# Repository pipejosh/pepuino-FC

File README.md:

This the next gen FC designed for a rocket (it's still in progress)

## Schematic

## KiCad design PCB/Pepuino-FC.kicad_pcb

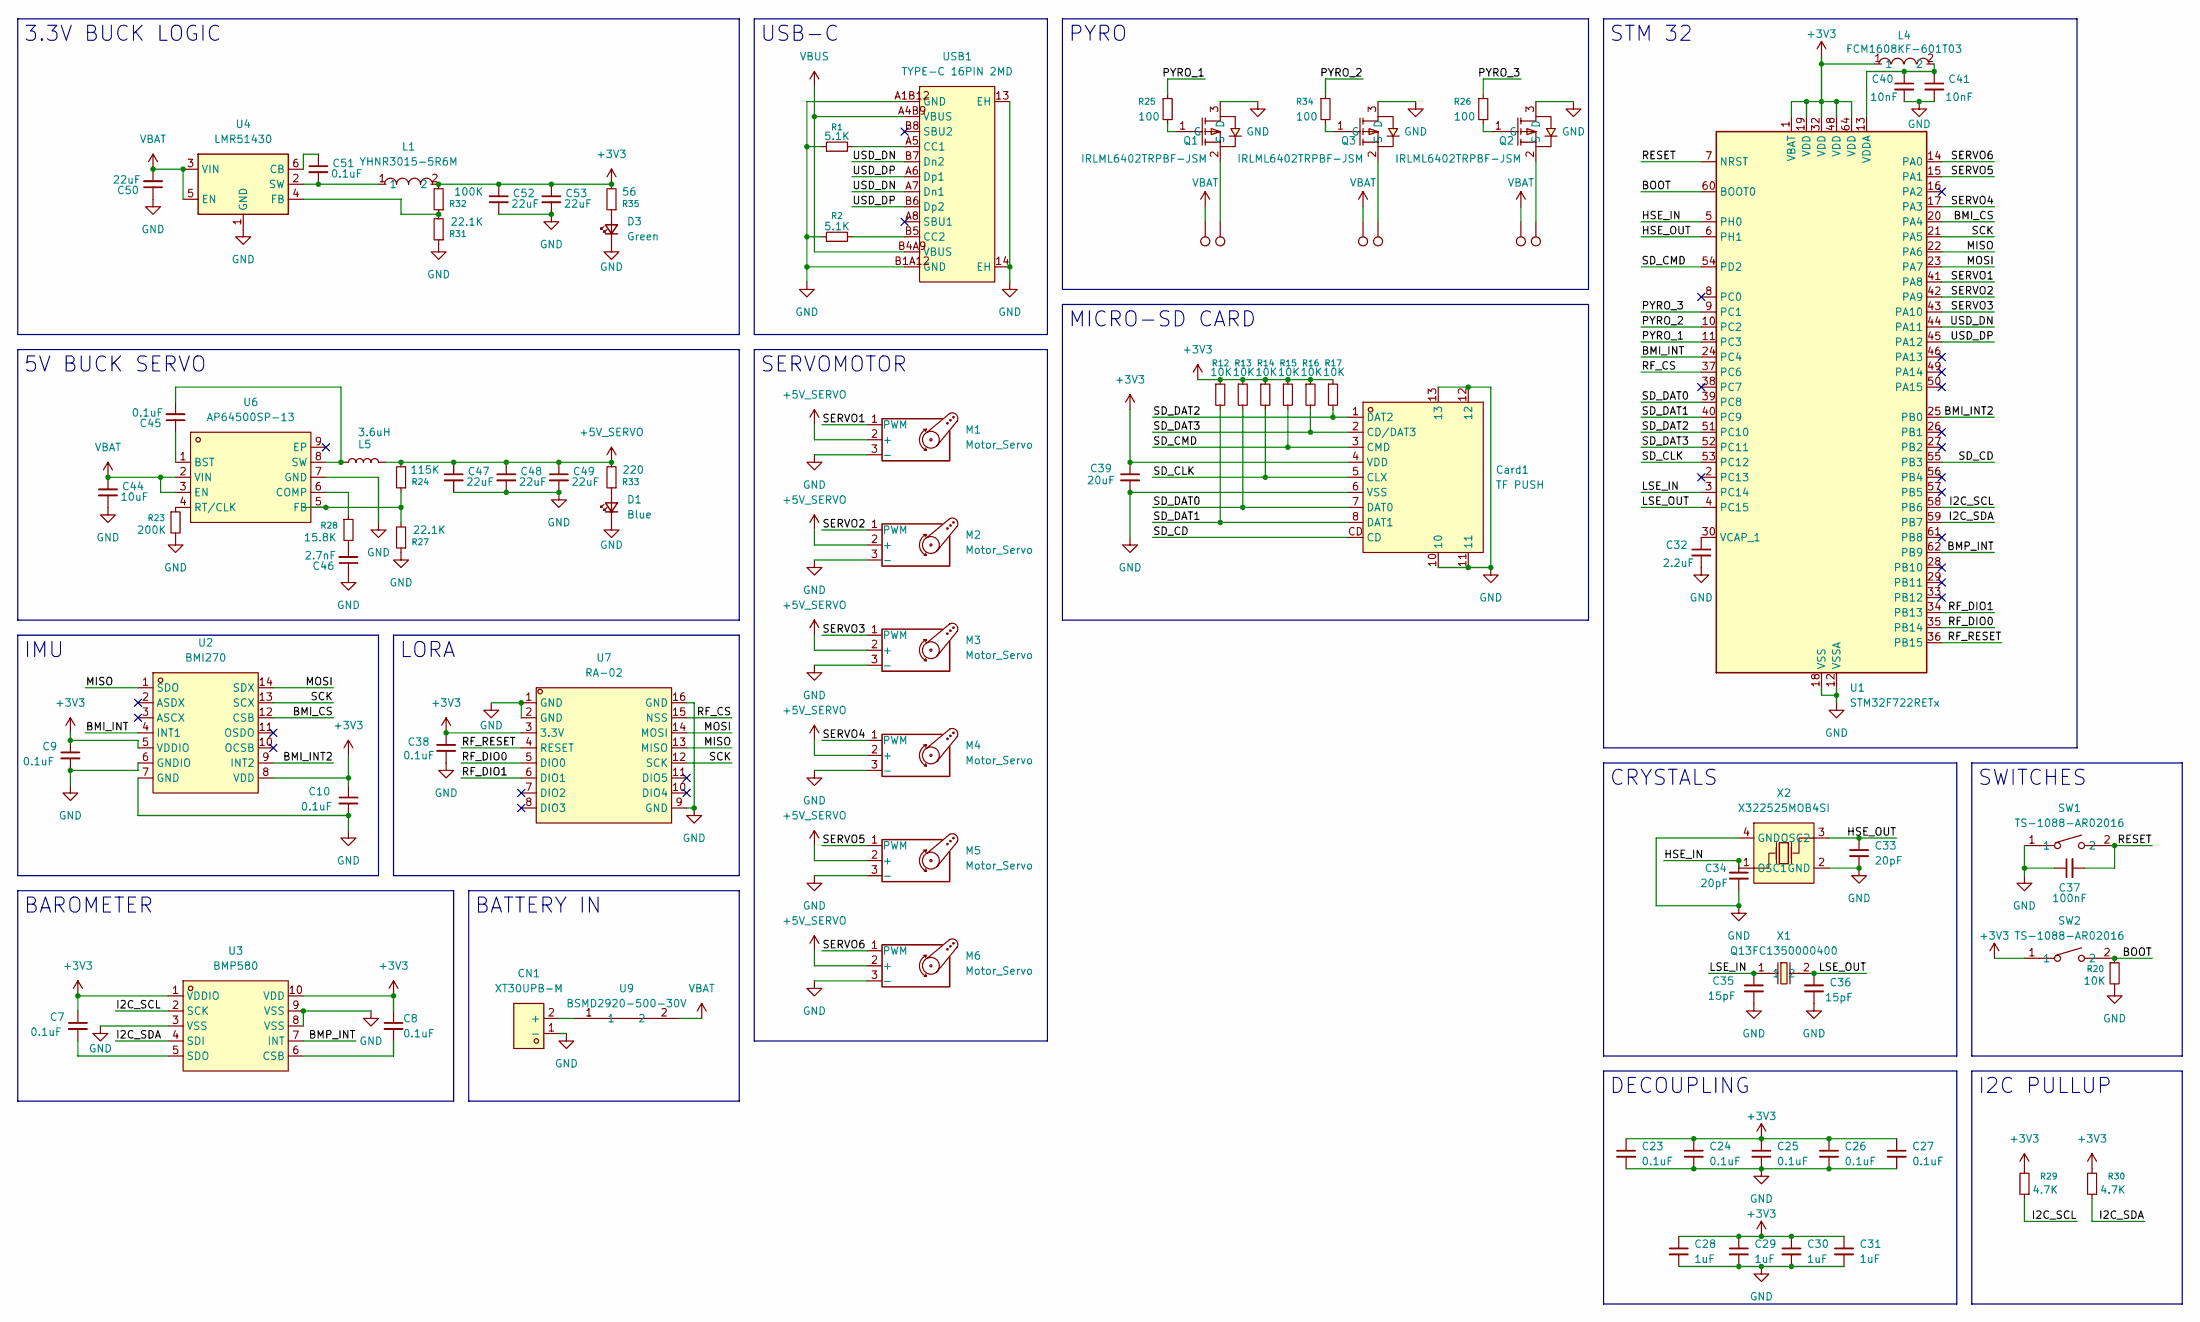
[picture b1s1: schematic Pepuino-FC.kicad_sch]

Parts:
C7, C8, C9, C10, C23, C24, C25, C26, C27, C38: 0.1uF; C_0402_1005Metric
C28, C29, C30, C31: 1uF; C_0402_1005Metric
C32: 2.2uF; C_0402_1005Metric
C33, C34: 20pF; C_0402_1005Metric
C35, C36: 15pF; C_0402_1005Metric
C37: 100nF; C_0402_1005Metric
C39: 20uF; C_0402_1005Metric
C40, C41: 10nF; C_0402_1005Metric
C44: 10uF; C_0805_2012Metric
C45, C51: 0.1uF; C_0805_2012Metric
C46: 2.7nF; C_0805_2012Metric
C47, C48, C49, C50, C52, C53: 22uF; C_0805_2012Metric
CN1: XT30UPB-M; CONN-TH_XT30UPB-M; MPN XT30UPB-M; LCSC Part C428721
Card1: TF PUSH; TF-SMD_TF-PUSH; MPN TF PUSH; LCSC Part C393941
D1: Blue; LED_0805_2012Metric
D3: Green; LED_0805_2012Metric
L1: YHNR3015-5R6M; IND-SMD_L3.0-W3.0; MPN YHNR3015-5R6M; LCSC Part C18236327
L4: FCM1608KF-601T03; L0603; MPN FCM1608KF-601T03; LCSC Part C141723
L5: 3.6uH; L_0402_1005Metric
M1, M2, M3, M4, M5, M6: Motor_Servo; PinHeader_1x03_P1.00mm_Vertical
Q1, Q2, Q3: IRLML6402TRPBF-JSM; SOT-23-3_L2.9-W1.3-P1.90-LS2.4-BR; MPN IRLML6402TRPBF-JSM; LCSC Part C18190991
R1, R2: 5.1K; R_0201_0603Metric
R12, R13, R14, R15, R16, R17, R20: 10K; R_0201_0603Metric
R23: 200K; R_0201_0603Metric
R24: 115K; R_0201_0603Metric
R25, R26, R34: 100; R_0201_0603Metric
R27, R31: 22.1K; R_0201_0603Metric
R28: 15.8K; R_0201_0603Metric
R29, R30: 4.7K; R_0201_0603Metric
R32: 100K; R_0201_0603Metric
R33: 220; R_0201_0603Metric
R35: 56; R_0201_0603Metric
SW1, SW2: TS-1088-AR02016; SW-SMD_L3.9-W3.0-P4.45; MPN TS-1088-AR02016; LCSC Part C720477
TP1, TP2, TP3, TP4, TP5, TP6: TestPoint; TestPoint_Pad_D2.0mm
U1: STM32F722RETx; LQFP-64_10x10mm_P0.5mm
U2: BMI270; LGA-14_L3.0-W2.5-P0.50-BR; MPN BMI270; LCSC Part C2836813
U3: BMP580; LGA-10_L2.0-W2.0-P0.50-TL_BMP580; MPN BMP580; LCSC Part C22391138
U4: LMR51430; SOT-23-6
U6: AP64500SP-13; SO-8_L4.9-W3.9-P1.27-LS6.0-BL-EP; MPN AP64500SP-13; LCSC Part C2070920
U7: RA-02; WIRELM-SMD_RA-02-BL; MPN Ra-02; LCSC Part C90039
U9: BSMD2920-500-30V; F2920; MPN BSMD2920-500-30V; LCSC Part C20539728
USB1: TYPE-C 16PIN 2MD; USB-C-SMD_TYPE-C-16PIN-2MD-073; MPN TYPE-C 16PIN 2MD(073); LCSC Part C2765186
X1: Q13FC1350000400; FC-135R_L3.2-W1.5; MPN Q13FC13500004; LCSC Part C32346
X2: X322525MOB4SI; CRYSTAL-SMD_4P-L3.2-W2.5-BL; MPN X322525MOB4SI; LCSC Part C9006

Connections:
+3V3: C7.1, C8.1, C9.1, C10.1, C23.1, C24.1, C25.1, C26.1, C27.1, C28.1, C29.1, C30.1, C31.1, C38.1, C39.1, C52.1, C53.1, Card1.4 (VDD), L1.2, L4.1, R12.1, R13.1, R14.1, R15.1, R16.1, R17.1, R29.2, R30.2, R32.2, R35.2, SW2.1, U1.1 (VBAT), U1.19 (VDD), U1.32 (VDD), U1.48 (VDD), U1.64 (VDD), U2.5 (VDDIO), U2.8 (VDD), U3.1 (VDDIO), U3.10 (VDD), U7.3 (3.3V)
+5V_SERVO: C47.1, C48.1, C49.1, L5.2, M1.2 (+), M2.2 (+), M3.2 (+), M4.2 (+), M5.2 (+), M6.2 (+), R24.2, R33.2
/BMI_CS: U1.20 (PA4), U2.12 (CSB)
/BMI_INT: U1.24 (PC4), U2.4 (INT1)
/BMI_INT2: U1.25 (PB0), U2.9 (INT2)
/BMP_INT: U1.62 (PB9), U3.7 (INT)
/BOOT: R20.1, SW2.2, U1.60 (BOOT0)
/HSE_IN: C34.1, U1.5 (PH0), X2.1 (OSC1)
/HSE_OUT: C33.1, U1.6 (PH1), X2.3 (OSC2)
/I2C_SCL: R29.1, U1.58 (PB6), U3.2 (SCK)
/I2C_SDA: R30.1, U1.59 (PB7), U3.4 (SDI)
/LSE_IN: C35.1, U1.3 (PC14), X1.1
/LSE_OUT: C36.1, U1.4 (PC15), X1.2
/MISO: U1.22 (PA6), U2.1 (SDO), U7.13 (MISO)
/MOSI: U1.23 (PA7), U2.14 (SDX), U7.14 (MOSI)
/PYRO_1: R25.1, U1.11 (PC3)
/PYRO_2: R34.1, U1.10 (PC2)
/PYRO_3: R26.1, U1.9 (PC1)
/RESET: C37.2, SW1.2, U1.7 (NRST)
/RF_CS: U1.37 (PC6), U7.15 (NSS)
/RF_DIO0: U1.35 (PB14), U7.5 (DIO0)
/RF_DIO1: U1.34 (PB13), U7.6 (DIO1)
/RF_RESET: U1.36 (PB15), U7.4 (RESET)
/SCK: U1.21 (PA5), U2.13 (SCX), U7.12 (SCK)
/SD_CD: Card1.CD, U1.55 (PB3)
/SD_CLK: Card1.5 (CLX), R14.2, U1.53 (PC12)
/SD_CMD: Card1.3 (CMD), R15.2, U1.54 (PD2)
/SD_DAT0: Card1.7 (DAT0), R13.2, U1.39 (PC8)
/SD_DAT1: Card1.8 (DAT1), R12.2, U1.40 (PC9)
/SD_DAT2: Card1.1 (DAT2), R17.2, U1.51 (PC10)
/SD_DAT3: Card1.2 (CD/DAT3), R16.2, U1.52 (PC11)
/SERVO1: M1.1 (PWM), U1.41 (PA8)
/SERVO2: M2.1 (PWM), U1.42 (PA9)
/SERVO3: M3.1 (PWM), U1.43 (PA10)
/SERVO4: M4.1 (PWM), U1.17 (PA3)
/SERVO5: M5.1 (PWM), U1.15 (PA1)
/SERVO6: M6.1 (PWM), U1.14 (PA0)
/USD_DN: U1.44 (PA11), USB1.A7 (Dn1), USB1.B7 (Dn2)
/USD_DP: U1.45 (PA12), USB1.A6 (Dp1), USB1.B6 (Dp2)
GND: C9.2, C10.2, C23.2, C24.2, C25.2, C26.2, C27.2, C28.2, C29.2, C30.2, C31.2, C32.2, C33.2, C34.2, C35.2, C36.2, C37.1, C38.2, C39.2, C40.2, C41.2, C44.2, C46.1, C47.2, C48.2, C49.2, C50.1, C52.2, C53.2, CN1.1 (-), Card1.6 (VSS), Card1.10, Card1.11, Card1.12, Card1.13, D1.1 (K), D3.1 (K), M1.3 (-), M2.3 (-), M3.3 (-), M4.3 (-), M5.3 (-), M6.3 (-), Q1.3 (D), Q2.3 (D), Q3.3 (D), R1.1, R2.1, R20.2, R23.2, R27.1, R31.1, SW1.1, U1.12 (VSSA), U1.18 (VSS), U1.31 (VSS), U1.47 (VSS), U1.63 (VSS), U2.6 (GNDIO), U2.7 (GND), U3.3 (VSS), U3.8 (VSS), U3.9 (VSS), U4.1 (GND), U6.7 (GND), U7.1 (GND), U7.2 (GND), U7.9 (GND), U7.16 (GND), USB1.13 (EH), USB1.14 (EH), USB1.A1B12 (GND), USB1.B1A12 (GND), X2.2 (GND), X2.4 (GND)
unnamed: C46.2, R28.2
unnamed: CN1.2 (+), U9.1
unnamed: D1.2 (A), R33.1
unnamed: D3.2 (A), R35.1
unnamed: Q1.1 (G), R25.2
unnamed: Q1.2 (S), TP4.1 (1_1)
unnamed: Q2.1 (G), R26.2
unnamed: Q2.2 (S), TP1.1 (1_1)
unnamed: Q3.1 (G), R34.2
unnamed: Q3.2 (S), TP6.1 (1_1)
unnamed: C32.1, U1.30 (VCAP_1)
unnamed: C40.1, C41.1, L4.2, U1.13 (VDDA)
unnamed: C8.2, U3.6 (CSB)
unnamed: C7.2, U3.5 (SDO)
unnamed: C51.1, U4.6 (CB)
unnamed: R31.2, R32.1, U4.4 (FB)
unnamed: C51.2, L1.1, U4.2 (SW)
unnamed: C45.1, U6.1 (BST)
unnamed: R28.1, U6.6 (COMP)
unnamed: R24.1, R27.2, U6.5 (FB)
unnamed: R23.1, U6.4 (RT/CLK)
unnamed: C45.2, L5.1, U6.8 (SW)
unnamed: R1.2, USB1.A5 (CC1)
unnamed: R2.2, USB1.B5 (CC2)
VBAT: C44.1, C50.2, TP2.1 (1_1), TP3.1 (1_1), TP5.1 (1_1), U4.3 (VIN), U4.5 (EN), U6.2 (VIN), U6.3 (EN), U9.2
VBUS: USB1.A4B9 (VBUS), USB1.B4A9 (VBUS)

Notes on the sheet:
SERVOMOTOR
I2C PULLUP
USB-C
5V BUCK SERVO
BATTERY IN
LORA
BAROMETER
DECOUPLING
CRYSTALS
SWITCHES
PYRO
STM 32
3.3V BUCK LOGIC
MICRO-SD CARD
IMU

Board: 4 copper layers, 93 parts (0 on the bottom side), 66 nets, no tracks yet.

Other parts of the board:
H1, H2, H3, H4: MountingScrew; MountingHole_2.2mm_M2_DIN965_Pad

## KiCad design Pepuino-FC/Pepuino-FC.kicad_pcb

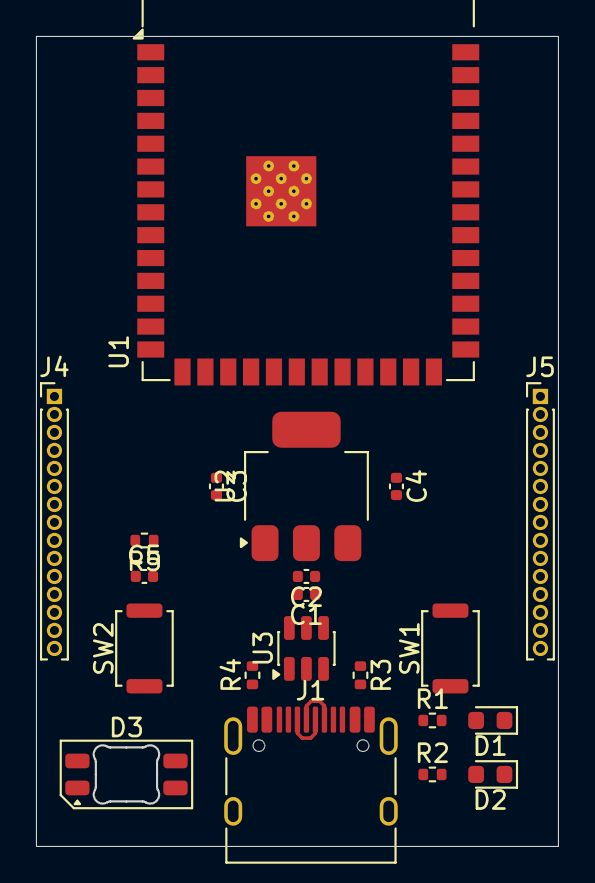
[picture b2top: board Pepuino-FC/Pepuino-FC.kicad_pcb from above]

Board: 2 copper layers, 28.9 x 44.9 mm, 21 parts (0 on the bottom side), 34 nets.

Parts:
C1, C4: 100n; C_0402_1005Metric
C2, C5: 10u; C_0402_1005Metric
C3: 22u; C_0402_1005Metric
D1, D2: LED; LED_0603_1608Metric
D3: SK6812MINI-E; LED_SK6812MINI-E_3.2x2.8mm_P1.5mm_ReverseMount
J1: USB_C_Receptacle_USB2.0_16P; USB_C_Receptacle_HRO_TYPE-C-31-M-12
J4, J5: Conn_01x15_Pin; PinHeader_1x15_P1.00mm_Vertical
R1, R2, R3, R4, R5: 5.1K; R_0402_1005Metric
SW1, SW2: Switch; SW_Push_SPST_NO_Alps_SKRK
U1: ESP32-S3-WROOM-1
U2: LD1117S33TR_SOT223; SOT-223-3_TabPin2
U3: USBLC6-2SC6; SOT-23-6

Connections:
+3V3: C2.1, C3.1, C4.1, J4.2, J5.2, R2.1, R5.1, U2.2 (VO)
D+: U1.14 (USB_D+), U3.4 (I/O2)
D-: U1.13 (USB_D-), U3.6 (I/O1)
EN: C5.1, J4.4, R5.2, SW2.2, U1.3 (EN)
GND: C1.2, C2.2, C3.2, C4.2, C5.2, D1.1 (K), D2.1 (K), D3.1 (VSS), J1.A1 (GND), J1.A12 (GND), J1.B1 (GND), J1.B12 (GND), J1.SH (SHIELD), J4.1, J4.15, J5.1, J5.15, R3.1, R4.2, SW1.1, SW2.1, U1.1 (GND), U1.40 (GND), U1.41 (GND), U2.1 (GND), U3.2 (GND)
GPIO0: SW1.2, U1.27 (IO0)
GPIO2: J5.4, U1.38 (IO2)
GPIO3: J4.14, U1.15 (IO3)
GPIO4: J4.5, U1.4 (IO4)
GPIO5: J4.6, U1.5 (IO5)
GPIO6: J4.7, U1.6 (IO6)
GPIO7: J4.8, U1.7 (IO7)
GPIO8: J4.13, U1.12 (IO8)
GPIO9: J5.14, U1.17 (IO9)
GPIO10: J5.13, U1.18 (IO10)
GPIO11: J5.12, U1.19 (IO11)
GPIO12: J5.11, U1.20 (IO12)
GPIO13: J5.10, U1.21 (IO13)
GPIO14: J5.9, U1.22 (IO14)
GPIO15: J4.9, U1.8 (IO15)
GPIO16: J4.10, U1.9 (IO16)
GPIO17: J4.11, U1.10 (IO17)
GPIO18: J4.12, U1.11 (IO18)
GPIO21: D3.2 (DIN), J5.8, U1.23 (IO21)
GPIO38: J5.5, U1.31 (IO38)
GPIO47: J5.7, U1.24 (IO47)
GPIO48: J5.6, U1.25 (IO48)
unnamed: D1.2 (A), R1.2
unnamed: D2.2 (A), R2.2
unnamed: J1.A5 (CC1), R4.1
unnamed: J1.B5 (CC2), R3.2
unnamed: J1.A6 (D+), J1.B6 (D+), U3.3 (I/O2)
unnamed: J1.A7 (D-), J1.B7 (D-), U3.1 (I/O1)
VBUS: C1.1, D3.3 (VDD), J1.A4 (VBUS), J1.A9 (VBUS), J1.B4 (VBUS), J1.B9 (VBUS), J4.3, J5.3, R1.1, U2.3 (VI), U3.5 (VBUS)

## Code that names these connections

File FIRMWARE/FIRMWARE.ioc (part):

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Mcu.Name=STM32F722R(C-E)Tx
Mcu.Package=LQFP64
Mcu.UserName=STM32F722RETx
PA0-WKUP.Signal=S_TIM2_CH1_ETR
PA1.Signal=S_TIM2_CH2
PA10.Signal=S_TIM1_CH3
PA11.Mode=Host_Only
PA11.Signal=USB_OTG_FS_DM
PA12.Mode=Host_Only
PA12.Signal=USB_OTG_FS_DP
PA2.Signal=S_TIM2_CH3
PA3.Signal=S_TIM2_CH4
PA4.GPIOParameters=GPIO_Label
PA4.GPIO_Label=ICM_CS
PA4.Mode=NSS_Signal_Hard_Output
PA4.Signal=SPI1_NSS
PA5.Mode=Full_Duplex_Master
PA5.Signal=SPI1_SCK
PA6.Mode=Full_Duplex_Master
PA6.Signal=SPI1_MISO
PA7.Mode=Full_Duplex_Master
PA7.Signal=SPI1_MOSI
PA8.Signal=S_TIM1_CH1
PA9.Signal=S_TIM1_CH2
PB0.GPIOParameters=GPIO_Label
PB0.GPIO_Label=ICM_INT2
PB0.Signal=GPXTI0
PB1.Signal=GPIO_Output
PB13.GPIOParameters=GPIO_Label
PB13.GPIO_Label=RF_DIO1
PB13.Signal=GPIO_Input
PB14.GPIOParameters=GPIO_Label
PB14.GPIO_Label=RF_DIO0
PB14.Signal=GPIO_Input
PB15.GPIOParameters=GPIO_Label
PB15.GPIO_Label=RF_RST
PB15.Signal=GPIO_Output
PB3.GPIOParameters=GPIO_Label
PB3.GPIO_Label=SD_CS
PB3.Signal=GPIO_Output
PB5.GPIOParameters=GPIO_Label
PB5.GPIO_Label=BQ_INT
PB5.Signal=GPXTI5
PB6.Mode=I2C
PB6.Signal=I2C1_SCL
PB7.Mode=I2C
PB7.Signal=I2C1_SDA
PB8.GPIOParameters=GPIO_Label
PB8.GPIO_Label=BQ_CE
PB8.Signal=GPIO_Output
PB9.GPIOParameters=GPIO_Label
PB9.GPIO_Label=BMP_INT
PB9.Signal=GPIO_Output
PC1.GPIOParameters=GPIO_Label
PC1.GPIO_Label=PYRO_2
PC1.Signal=GPIO_Output
PC10.Mode=SD_4_bits_Wide_bus
PC10.Signal=SDMMC1_D2
PC11.Mode=SD_4_bits_Wide_bus
PC11.Signal=SDMMC1_D3
PC12.Mode=SD_4_bits_Wide_bus
PC12.Signal=SDMMC1_CK
PC14-OSC32_IN.Mode=LSE-External-Oscillator
PC14-OSC32_IN.Signal=RCC_OSC32_IN
PC15-OSC32_OUT.Mode=LSE-External-Oscillator
PC15-OSC32_OUT.Signal=RCC_OSC32_OUT
PC2.GPIOParameters=GPIO_Label
PC2.GPIO_Label=PYRO_1
PC2.Signal=GPIO_Output
PC4.GPIOParameters=GPIO_Label
PC4.GPIO_Label=ICM_INT1
PC4.Signal=GPXTI4
PC6.GPIOParameters=GPIO_Label
PC6.GPIO_Label=RF_CS
PC6.Signal=GPIO_Output
PC8.Mode=SD_4_bits_Wide_bus
PC8.Signal=SDMMC1_D0
PC9.Mode=SD_4_bits_Wide_bus
PC9.Signal=SDMMC1_D1
PD2.Mode=SD_4_bits_Wide_bus
PD2.Signal=SDMMC1_CMD
PH0-OSC_IN.Mode=HSE-External-Oscillator
PH0-OSC_IN.Signal=RCC_OSC_IN
PH1-OSC_OUT.Mode=HSE-External-Oscillator
PH1-OSC_OUT.Signal=RCC_OSC_OUT
RCC.HSE_VALUE=25000000
board=custom

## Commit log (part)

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2026-04-28 add picture
2026-04-28 Add initial project description and schematic
2026-05-13 add pcb files and firmware files
2026-05-13 add schematic diagram image
2026-05-31 add pyro
